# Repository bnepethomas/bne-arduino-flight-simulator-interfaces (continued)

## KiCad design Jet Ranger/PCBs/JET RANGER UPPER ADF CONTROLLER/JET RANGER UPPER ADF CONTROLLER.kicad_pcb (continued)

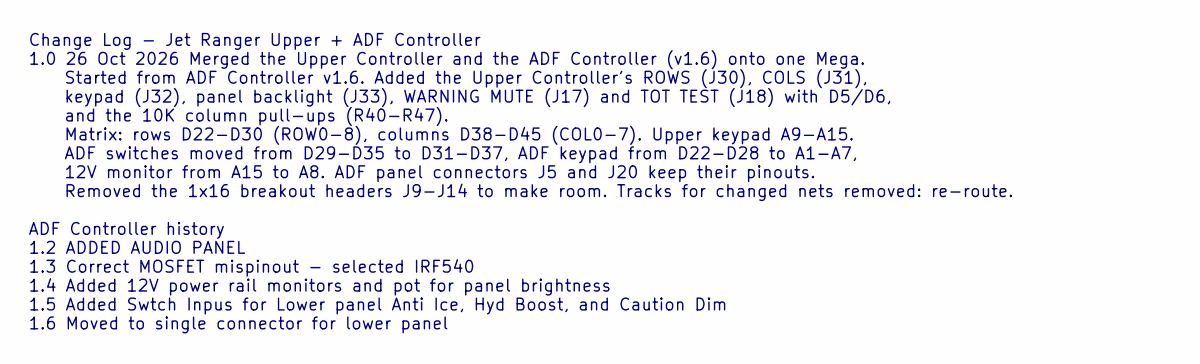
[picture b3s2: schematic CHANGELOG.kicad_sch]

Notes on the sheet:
Change Log - Jet Ranger Upper + ADF Controller 1.0 26 Oct 2026 Merged the Upper Controller and the ADF Controller (v1.6) onto one Mega. Started from ADF Controller v1.6. Added the Upper Controller's ROWS (J30), COLS (J31), keypad (J32), panel backlight (J33), WARNING MUTE (J17) and TOT TEST (J18) w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

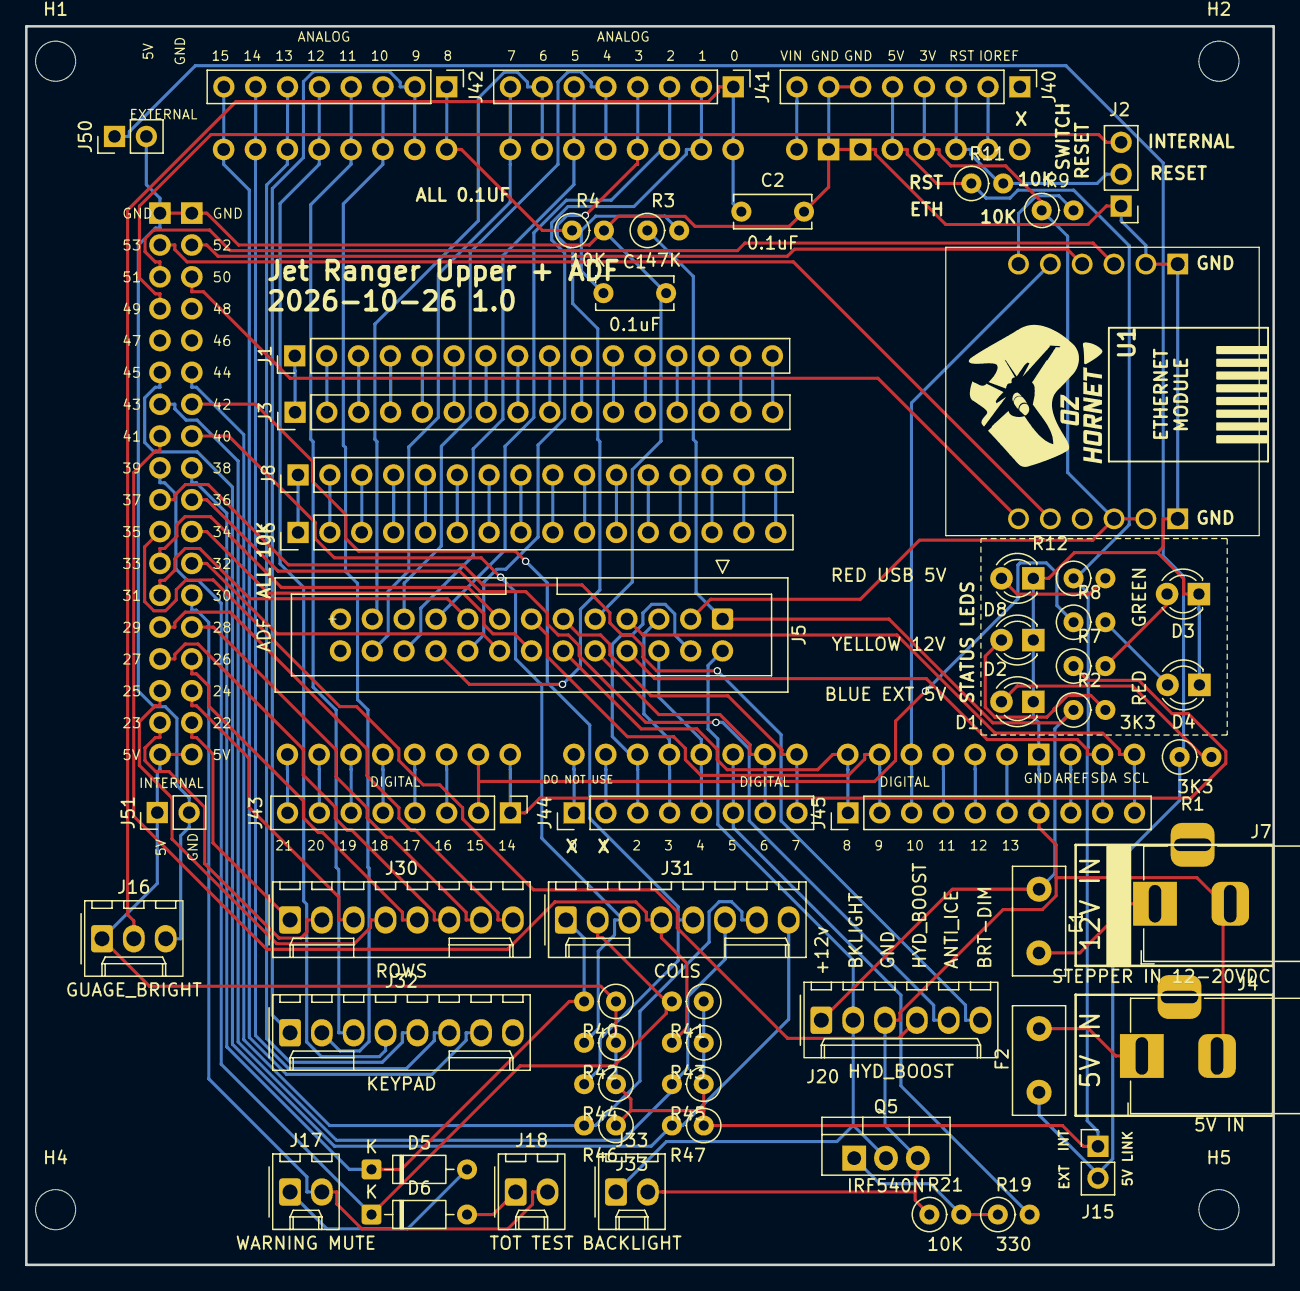
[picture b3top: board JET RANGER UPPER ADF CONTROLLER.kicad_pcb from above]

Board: 2 copper layers, 99.5 x 98.8 mm, 62 parts (0 on the bottom side), 122 nets.

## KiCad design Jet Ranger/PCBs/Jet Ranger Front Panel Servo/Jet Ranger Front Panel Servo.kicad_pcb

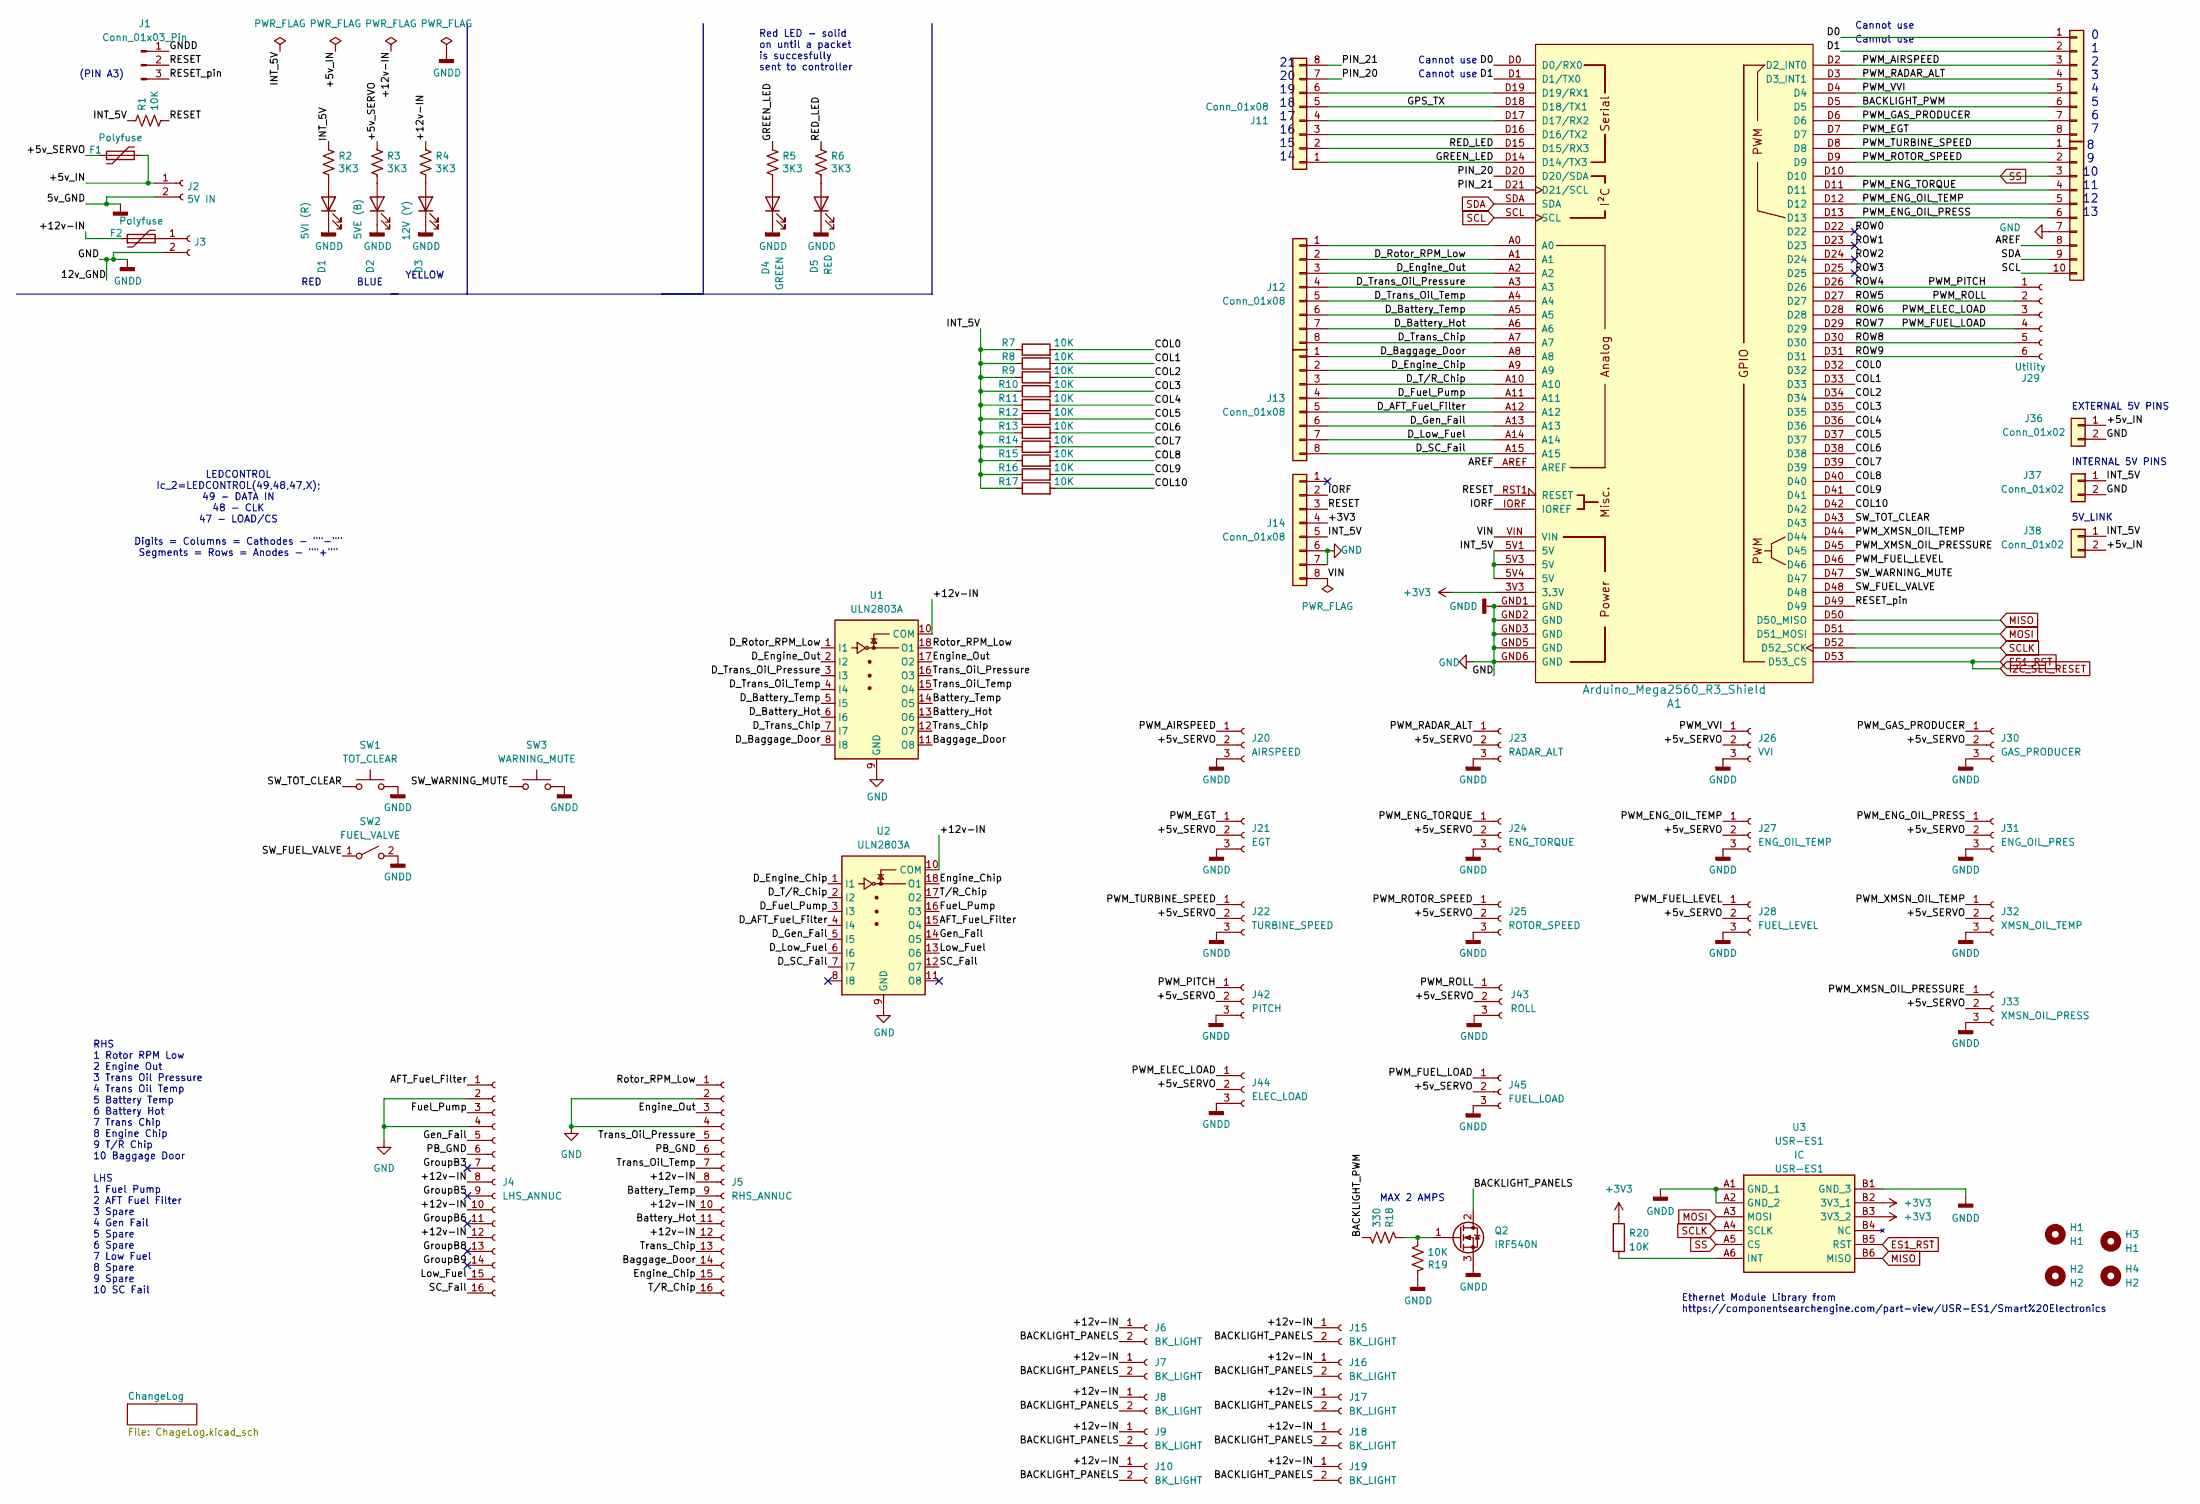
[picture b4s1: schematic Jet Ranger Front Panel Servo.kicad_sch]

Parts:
A1: Arduino_Mega2560_R3_Shield
D1: 5VI (R); LED_D3.0mm
D2: 5VE (B); LED_D3.0mm
D3: 12V (Y); LED_D3.0mm
D4: GREEN; LED_D3.0mm
D5: RED; LED_D3.0mm
F1, F2: Polyfuse; Fuse_Littelfuse_395Series
H1, H3: H1; MountingHole_3.2mm_M3
H2, H4: H2; MountingHole_3.2mm_M3
J1: Conn_01x03_Pin; PinHeader_1x03_P2.54mm_Vertical
J2: 5V IN; BarrelJack_Horizontal
J3: STEPPER IN 12-20VDC; BarrelJack_Horizontal
J4: LHS_ANNUC; IDC-Header_2x08_P2.54mm_Vertical
J5: RHS_ANNUC; IDC-Header_2x08_P2.54mm_Vertical
J6, J7, J8, J9, J10, J15, J16, J17, J18, J19: BK_LIGHT; Molex_KK-254_AE-6410-02A_1x02_P2.54mm_Vertical
J11, J12, J13, J14, J34: Conn_01x08; PinHeader_1x08_P2.54mm_Vertical
J20: AIRSPEED; PinHeader_1x03_P2.54mm_Vertical
J21: EGT; PinHeader_1x03_P2.54mm_Vertical
J22: TURBINE_SPEED; PinHeader_1x03_P2.54mm_Vertical
J23: RADAR_ALT; PinHeader_1x03_P2.54mm_Vertical
J24: ENG_TORQUE; PinHeader_1x03_P2.54mm_Vertical
J25: ROTOR_SPEED; PinHeader_1x03_P2.54mm_Vertical
J26: VVI; PinHeader_1x03_P2.54mm_Vertical
J27: ENG_OIL_TEMP; PinHeader_1x03_P2.54mm_Vertical
J28: FUEL_LEVEL; PinHeader_1x03_P2.54mm_Vertical
J29: Utility; PinHeader_1x06_P2.54mm_Vertical
J30: GAS_PRODUCER; PinHeader_1x03_P2.54mm_Vertical
J31: ENG_OIL_PRES; PinHeader_1x03_P2.54mm_Vertical
J32: XMSN_OIL_TEMP; PinHeader_1x03_P2.54mm_Vertical
J33: XMSN_OIL_PRESS; PinHeader_1x03_P2.54mm_Vertical
J35: Conn_01x10; PinHeader_1x10_P2.54mm_Vertical
J36, J37, J38: Conn_01x02; PinHeader_1x02_P2.54mm_Vertical
J42: PITCH; PinHeader_1x03_P2.54mm_Vertical
J43: ROLL; PinHeader_1x03_P2.54mm_Vertical
J44: ELEC_LOAD; PinHeader_1x03_P2.54mm_Vertical
J45: FUEL_LOAD; PinHeader_1x03_P2.54mm_Vertical
Q2: IRF540N; TO-220-3_Vertical
R1, R7, R8, R9, R10, R11, R12, R13, R14, R15, R16, R17, R19, R20: 10K; R_Axial_DIN0207_L6.3mm_D2.5mm_P2.54mm_Vertical
R2, R3, R4, R5, R6: 3K3; R_Axial_DIN0207_L6.3mm_D2.5mm_P2.54mm_Vertical
R18: 330; R_Axial_DIN0207_L6.3mm_D2.5mm_P2.54mm_Vertical
SW1: TOT_CLEAR; Molex_KK-254_AE-6410-02A_1x02_P2.54mm_Vertical
SW2: FUEL_VALVE; Molex_KK-254_AE-6410-02A_1x02_P2.54mm_Vertical
SW3: WARNING_MUTE; Molex_KK-254_AE-6410-02A_1x02_P2.54mm_Vertical
U1, U2: ULN2803A; DIP-18_W7.62mm
U3: USR-ES1; USRES1; Manufacturer_Part_Number USR-ES1

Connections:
+3V3: A1.3V3 (3.3V), J14.4, R20.1, U3.B2 (3V3_1), U3.B3 (3V3_2)
/+5v_IN: F1.2, J2.1, J36.1, J38.2
/+5v_SERVO: F1.1, J20.2, J21.2, J22.2, J23.2, J24.2, J25.2, J26.2, J27.2, J28.2, J30.2, J31.2, J32.2, J33.2, J42.2, J43.2, J44.2, J45.2, R3.1
/+12v-IN: F2.1, J4.8, J4.10, J4.12, J5.8, J5.10, J5.12, J6.1, J7.1, J8.1, J9.1, J10.1, J15.1, J16.1, J17.1, J18.1, J19.1, R4.1, U1.10 (COM), U2.10 (COM)
/AFT_Fuel_Filter: J4.1, U2.15 (O4)
/AREF: A1.AREF, J35.8
/BACKLIGHT_PANELS: J6.2, J7.2, J8.2, J9.2, J10.2, J15.2, J16.2, J17.2, J18.2, J19.2, Q2.2 (D)
/BACKLIGHT_PWM: A1.D5, J34.6, R18.2
/Baggage_Door: J5.14, U1.11 (O8)
/Battery_Hot: J5.11, U1.13 (O6)
/Battery_Temp: J5.9, U1.14 (O5)
/COL0: A1.D32, R7.2
/COL1: A1.D33, R8.2
/COL2: A1.D34, R9.2
/COL3: A1.D35, R10.2
/COL4: A1.D36, R11.2
/COL5: A1.D37, R12.2
/COL6: A1.D38, R13.2
/COL7: A1.D39, R14.2
/COL8: A1.D40, R15.2
/COL9: A1.D41, R16.2
/COL10: A1.D42, R17.2
/D0: A1.D0 (D0/RX0), J34.1
/D1: A1.D1 (D1/TX0), J34.2
/D_AFT_Fuel_Filter: A1.A12, J13.5, U2.4 (I4)
/D_Baggage_Door: A1.A8, J13.1, U1.8 (I8)
/D_Battery_Hot: A1.A6, J12.7, U1.6 (I6)
/D_Battery_Temp: A1.A5, J12.6, U1.5 (I5)
/D_Engine_Chip: A1.A9, J13.2, U2.1 (I1)
/D_Engine_Out: A1.A2, J12.3, U1.2 (I2)
/D_Fuel_Pump: A1.A11, J13.4, U2.3 (I3)
/D_Gen_Fail: A1.A13, J13.6, U2.5 (I5)
/D_Low_Fuel: A1.A14, J13.7, U2.6 (I6)
/D_Rotor_RPM_Low: A1.A1, J12.2, U1.1 (I1)
/D_SC_Fail: A1.A15, J13.8, U2.7 (I7)
/D_Trans_Chip: A1.A7, J12.8, U1.7 (I7)
/D_Trans_Oil_Pressure: A1.A3, J12.4, U1.3 (I3)
/D_Trans_Oil_Temp: A1.A4, J12.5, U1.4 (I4)
/D_T/R_Chip: A1.A10, J13.3, U2.2 (I2)
/Engine_Chip: J5.15, U2.18 (O1)
/Engine_Out: J5.3, U1.17 (O2)
/Fuel_Pump: J4.3, U2.16 (O3)
/GPS_TX: A1.D18 (D18/TX1), J11.5
/GREEN_LED: A1.D14 (D14/TX3), J11.1, R5.1
/Gen_Fail: J4.5, U2.14 (O5)
/GroupB3: J4.7
/GroupB5: J4.9
/GroupB6: J4.11
/GroupB8: J4.13
/GroupB9: J4.14
/INT_5V: A1.5V1 (5V), A1.5V3 (5V), A1.5V4 (5V), J14.5, J37.1, J38.1, R1.1, R2.1, R7.1, R8.1, R9.1, R10.1, R11.1, R12.1, R13.1, R14.1, R15.1, R16.1, R17.1
/IORF: A1.IORF (IOREF), J14.2
/Low_Fuel: J4.15, U2.13 (O6)
/PB_GND: J4.6, J5.6
/PIN_20: A1.D20 (D20/SDA), J11.7
/PIN_21: A1.D21 (D21/SCL), J11.8
/PWM_AIRSPEED: A1.D2 (D2_INT0), J20.1, J34.3
/PWM_EGT: A1.D7, J21.1, J34.8
/PWM_ELEC_LOAD: A1.D28, J29.3, J44.1
/PWM_ENG_OIL_PRESS: A1.D13, J31.1, J35.6
/PWM_ENG_OIL_TEMP: A1.D12, J27.1, J35.5
/PWM_ENG_TORQUE: A1.D11, J24.1, J35.4
/PWM_FUEL_LEVEL: A1.D46, J28.1
/PWM_FUEL_LOAD: A1.D29, J29.4, J45.1
/PWM_GAS_PRODUCER: A1.D6, J30.1, J34.7
/PWM_PITCH: A1.D26, J29.1, J42.1
/PWM_RADAR_ALT: A1.D3 (D3_INT1), J23.1, J34.4
/PWM_ROLL: A1.D27, J29.2, J43.1
/PWM_ROTOR_SPEED: A1.D9, J25.1, J35.2
/PWM_TURBINE_SPEED: A1.D8, J22.1, J35.1
/PWM_VVI: A1.D4, J26.1, J34.5
/PWM_XMSN_OIL_PRESSURE: A1.D45, J33.1
/PWM_XMSN_OIL_TEMP: A1.D44, J32.1
/RED_LED: A1.D15 (D15/RX3), J11.2, R6.1
/RESET: A1.RST1 (RESET), J1.2, J14.3, R1.2
/RESET_pin: A1.D49, J1.3
/ROW0: A1.D22
/ROW1: A1.D23
/ROW2: A1.D24
/ROW3: A1.D25
/ROW8: A1.D30, J29.5
/ROW9: A1.D31, J29.6
/Rotor_RPM_Low: J5.1, U1.18 (O1)
/SC_Fail: J4.16, U2.12 (O7)
/SW_FUEL_VALVE: A1.D48, SW2.1 (A)
/SW_TOT_CLEAR: A1.D43, SW1.1
/SW_WARNING_MUTE: A1.D47, SW3.1
/Trans_Chip: J5.13, U1.12 (O7)
/Trans_Oil_Pressure: J5.5, U1.16 (O3)
/Trans_Oil_Temp: J5.7, U1.15 (O4)
/T/R_Chip: J5.16, U2.17 (O2)
/VIN: A1.VIN, J14.8
ES1_RST: A1.D53 (D53_CS), U3.B5 (RST)
GND: A1.GND1 (GND), A1.GND2 (GND), A1.GND3 (GND), A1.GND5 (GND), A1.GND6 (GND), D1.1 (K), D2.1 (K), D3.1 (K), D4.1 (K), D5.1 (K), J1.1, J2.2, J3.2, J4.2, J4.4, J5.2, J5.4, J14.6, J14.7, J20.3, J21.3, J22.3, J23.3, J24.3, J25.3, J26.3, J27.3, J28.3, J30.3, J31.3, J32.3, J33.3, J35.7, J36.2, J37.2, J42.3, J43.3, J44.3, J45.3, Q2.3 (S), R19.1, SW1.2, SW2.2 (B), SW3.2, U1.9 (GND), U2.9 (GND), U3.A1 (GND_1), U3.A2 (GND_2), U3.B1 (GND_3)
MISO: A1.D50 (D50_MISO), U3.B6 (MISO)
MOSI: A1.D51 (D51_MOSI), U3.A3 (MOSI)
unnamed: A1.D16 (D16/TX2), J11.3
unnamed: A1.D17 (D17/RX2), J11.4
unnamed: A1.D19 (D19/RX1), J11.6
unnamed: D1.2 (A), R2.2
unnamed: D2.2 (A), R3.2
unnamed: D3.2 (A), R4.2
unnamed: D4.2 (A), R5.2
unnamed: D5.2 (A), R6.2
unnamed: F2.2, J3.1
unnamed: A1.A0, J12.1
unnamed: Q2.1 (G), R18.1, R19.2
unnamed: R20.2, U3.A6 (INT)
SCL: A1.SCL, J35.10
SCLK: A1.D52 (D52_SCK), U3.A4 (SCLK)
SDA: A1.SDA, J35.9
SS: A1.D10, J35.3, U3.A5 (CS)

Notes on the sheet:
YELLOW
MAX 2 AMPS
BLUE
INTERNAL 5V PINS
Ethernet Module Library from https://componentsearchengine.com/part-view/USR-ES1/Smart%20Electronics
Cannot use
RED
(PIN A3)
0 1 2 3 4 5 6 7
LEDCONTROL Ic_2=LEDCONTROL(49,48,47,X); 49 - DATA IN 48 - CLK 47 - LOAD/CS Digits = Columns = Cathodes - ""-"" Segments = Rows = Anodes - ""+""
Red LED - solid on until a packet is succesfully sent to controller
RHS 1 Rotor RPM Low 2 Engine Out 3 Trans Oil Pressure 4 Trans Oil Temp 5 Battery Temp 6 Battery Hot 7 Trans Chip 8 Engine Chip 9 T/R Chip 10 Baggage Door LHS 1 Fuel Pump 2 AFT Fuel Filter 3 Spare 4 Gen Fail 5 Spare 6 Spare 7 Low Fuel 8 Spare 9 Spare 10 SC Fail
5V_LINK
21 20 19 18 17 16 15 14
EXTERNAL 5V PINS
8 9 10 11 12 13

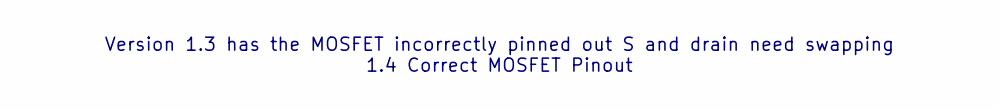
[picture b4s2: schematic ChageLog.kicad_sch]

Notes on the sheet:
Version 1.3 has the MOSFET incorrectly pinned out S and drain need swapping 1.4 Correct MOSFET Pinout

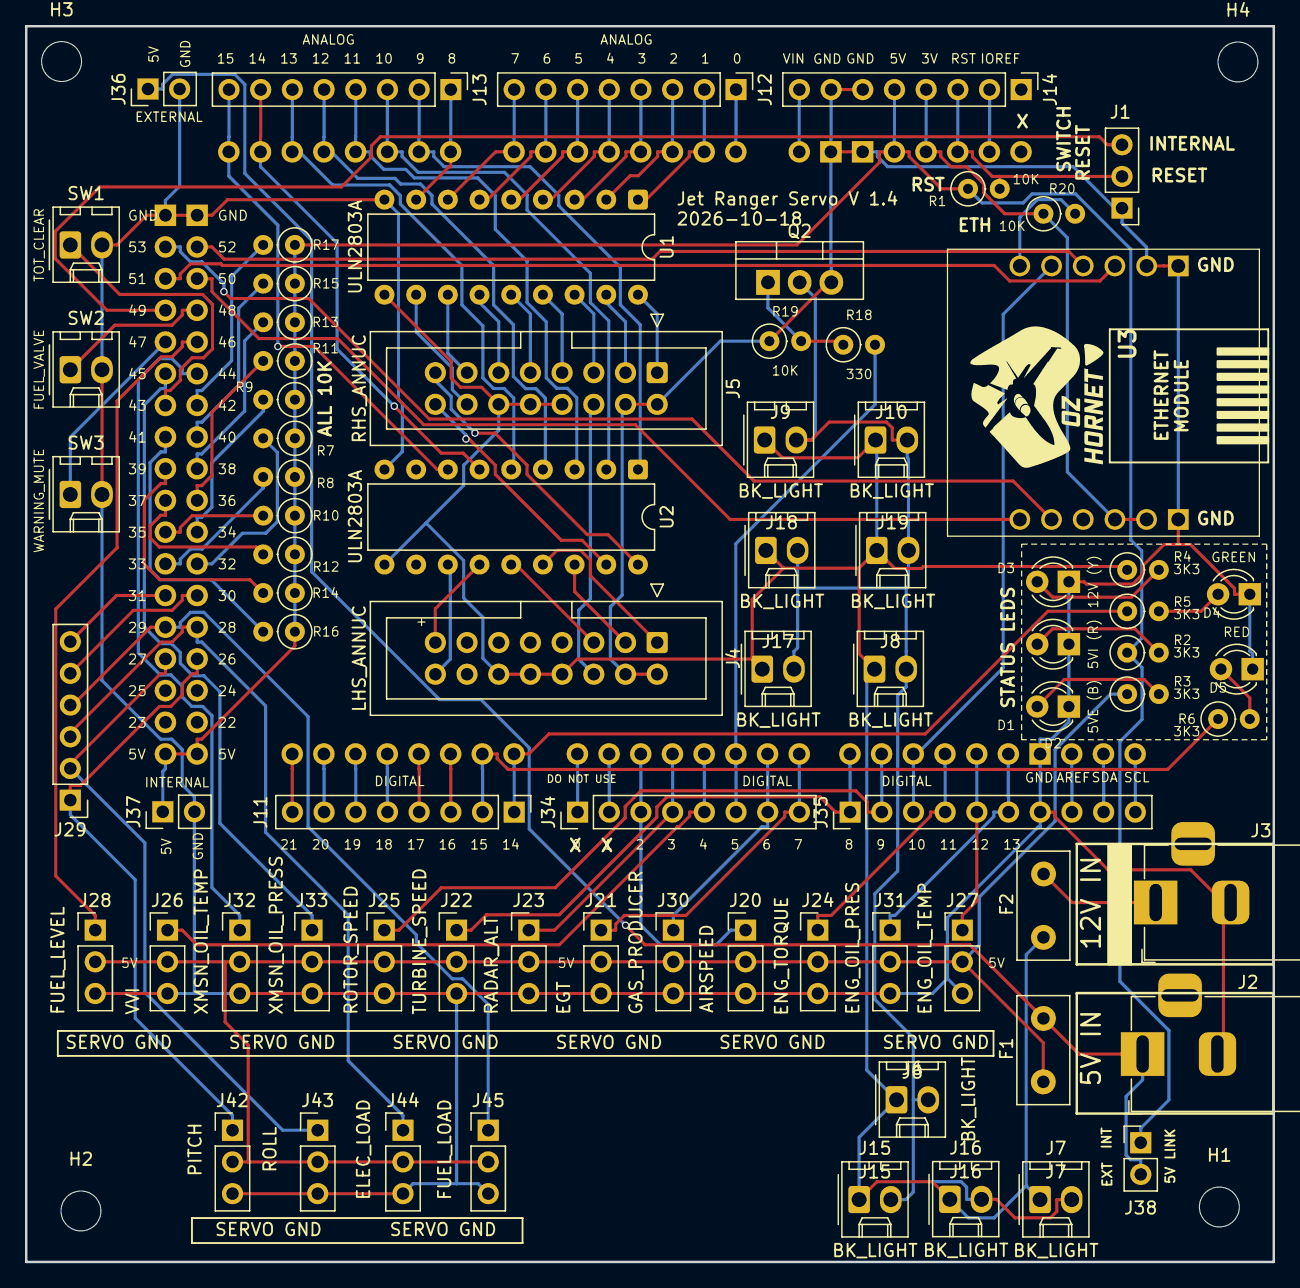
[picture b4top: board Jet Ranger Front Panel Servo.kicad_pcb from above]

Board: 2 copper layers, 100.0 x 99.1 mm, 81 parts (0 on the bottom side), 103 nets.

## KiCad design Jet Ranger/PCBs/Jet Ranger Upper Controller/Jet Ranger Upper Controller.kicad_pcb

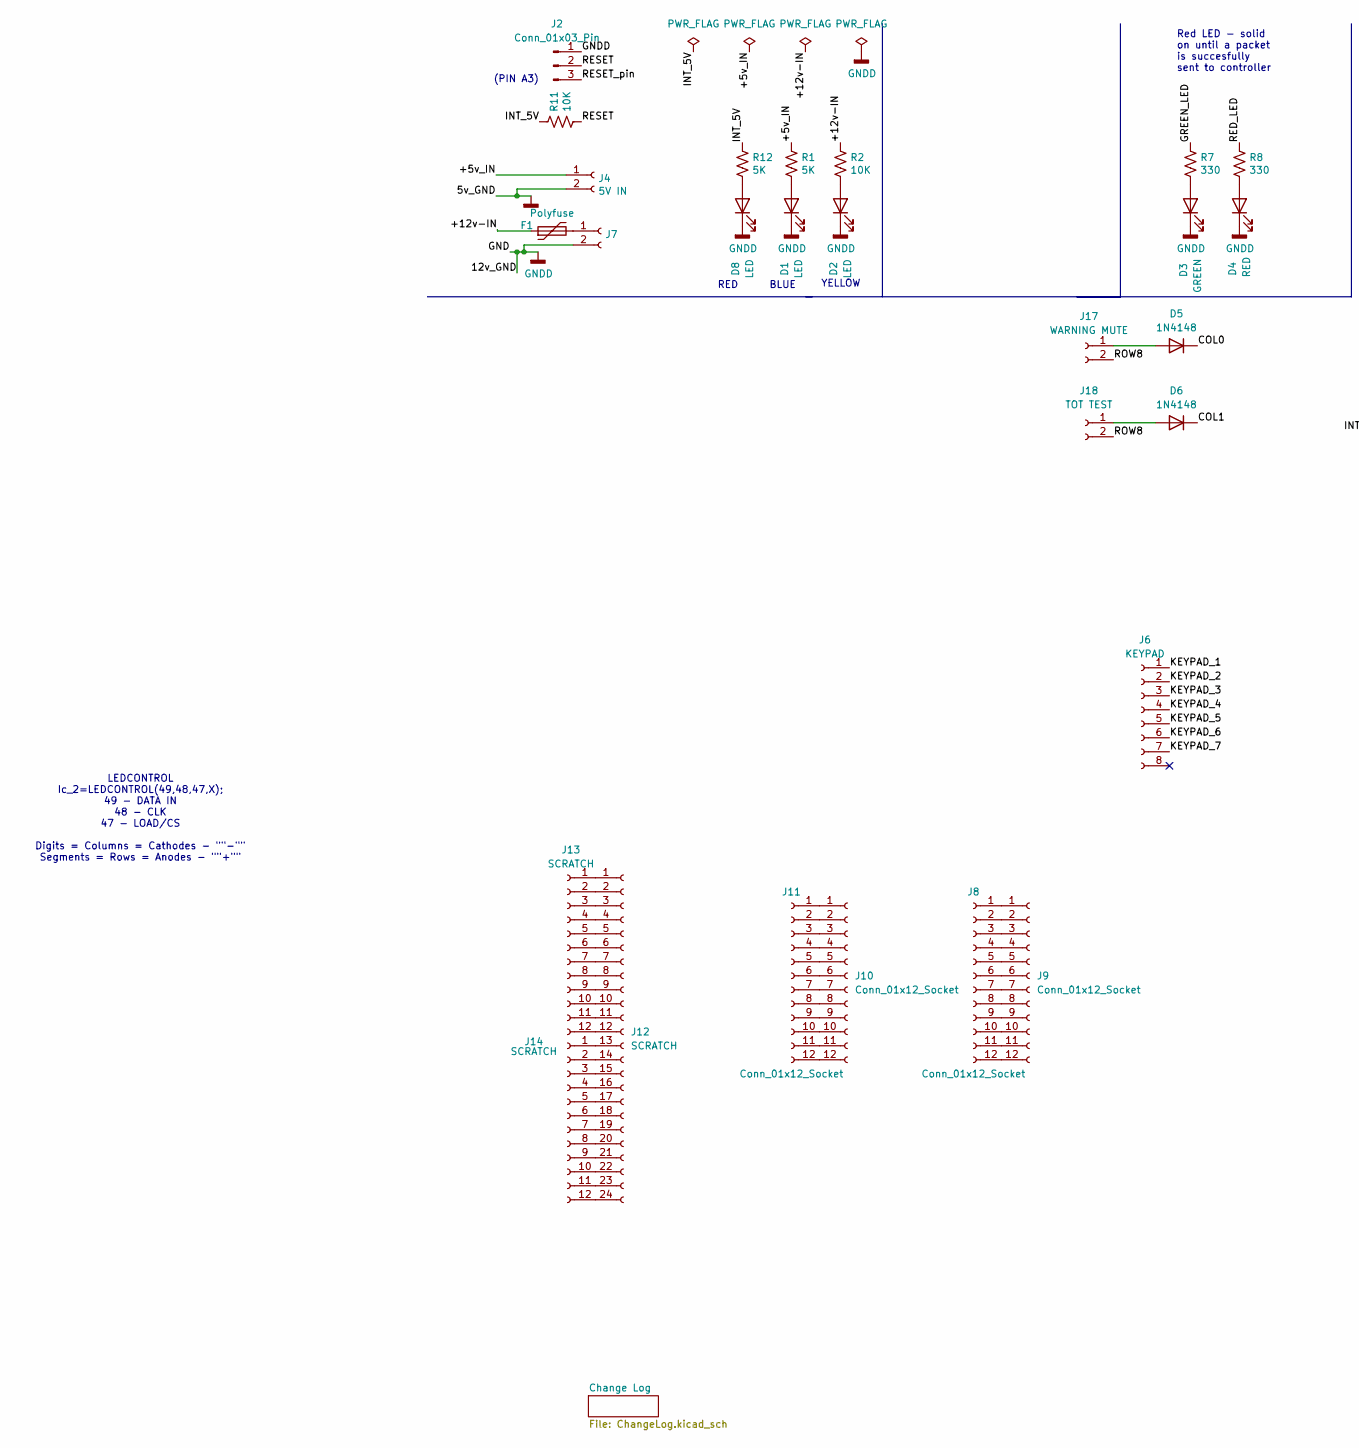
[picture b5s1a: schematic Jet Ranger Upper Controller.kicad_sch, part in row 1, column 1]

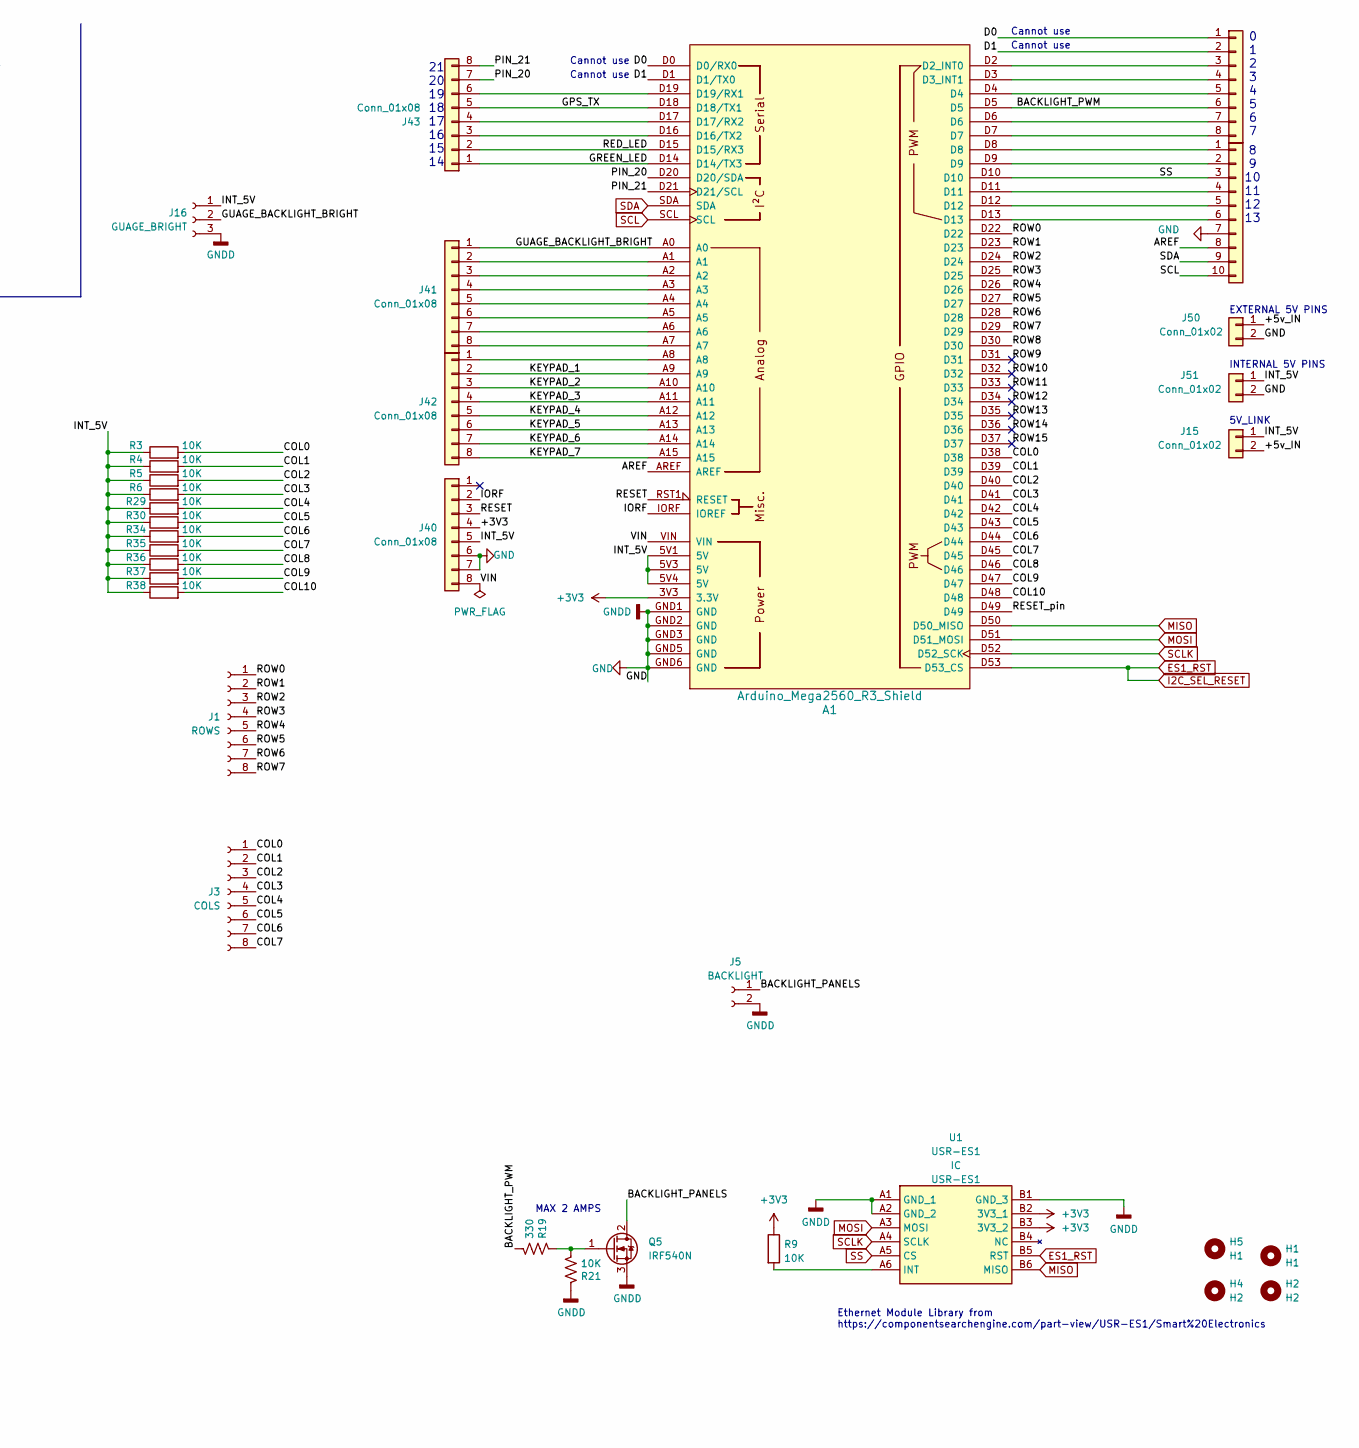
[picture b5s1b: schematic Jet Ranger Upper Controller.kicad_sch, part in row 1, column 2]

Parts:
A1: Arduino_Mega2560_R3_Shield
D1, D2, D8: LED; LED_D3.0mm
D3: GREEN; LED_D3.0mm
D4: RED; LED_D3.0mm
D5, D6: 1N4148; D_DO-35_SOD27_P7.62mm_Horizontal
F1: Polyfuse; Fuse_Bourns_MF-RG400
H1, H5: H1; MountingHole_3.2mm_M3
H2, H4: H2; MountingHole_3.2mm_M3
J1: ROWS; Molex_KK-254_AE-6410-08A_1x08_P2.54mm_Vertical
J2: Conn_01x03_Pin; PinHeader_1x03_P2.54mm_Vertical
J3: COLS; Molex_KK-254_AE-6410-08A_1x08_P2.54mm_Vertical
J4: 5V IN; BarrelJack_Horizontal
J5: BACKLIGHT; Molex_KK-254_AE-6410-02A_1x02_P2.54mm_Vertical
J6: KEYPAD; Molex_KK-254_AE-6410-08A_1x08_P2.54mm_Vertical
J7: STEPPER IN 12-20VDC; BarrelJack_Horizontal
J8, J9, J10, J11: Conn_01x12_Socket; PinHeader_1x12_P2.54mm_Vertical
J12: SCRATCH; IDC-Header_2x12_P2.54mm_Vertical
J13, J14: SCRATCH; PinHeader_1x12_P2.54mm_Vertical
J15, J50, J51: Conn_01x02; PinHeader_1x02_P2.54mm_Vertical
J16: GUAGE_BRIGHT; Molex_KK-254_AE-6410-03A_1x03_P2.54mm_Vertical
J17: WARNING MUTE; Molex_KK-254_AE-6410-02A_1x02_P2.54mm_Vertical
J18: TOT TEST; Molex_KK-254_AE-6410-02A_1x02_P2.54mm_Vertical
J40, J41, J42, J43, J44: Conn_01x08; PinHeader_1x08_P2.54mm_Vertical
J45: Conn_01x10; PinHeader_1x10_P2.54mm_Vertical
Q5: IRF540N; TO-220-3_Vertical
R1, R12: 5K; R_Axial_DIN0207_L6.3mm_D2.5mm_P2.54mm_Vertical
R2, R3, R4, R5, R6, R9, R11, R21, R29, R30, R34, R35, R36, R37, R38: 10K; R_Axial_DIN0207_L6.3mm_D2.5mm_P2.54mm_Vertical
R7, R8, R19: 330; R_Axial_DIN0207_L6.3mm_D2.5mm_P2.54mm_Vertical
U1: USR-ES1; USRES1; Manufacturer_Part_Number USR-ES1

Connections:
+3V3: A1.3V3 (3.3V), J40.4, R9.1, U1.B2 (3V3_1), U1.B3 (3V3_2)
/+5v_IN: J4.1, J15.2, J50.1, R1.1
/+12v-IN: F1.1, R2.1
/AREF: A1.AREF, J45.8
/BACKLIGHT_PANELS: J5.1, Q5.2 (D)
/BACKLIGHT_PWM: A1.D5, J44.6, R19.2
/COL0: A1.D38, D5.1 (K), J3.1, R3.2
/COL1: A1.D39, D6.1 (K), J3.2, R4.2
/COL2: A1.D40, J3.3, R5.2
/COL3: A1.D41, J3.4, R6.2
/COL4: A1.D42, J3.5, R29.2
/COL5: A1.D43, J3.6, R30.2
/COL6: A1.D44, J3.7, R34.2
/COL7: A1.D45, J3.8, R35.2
/COL8: A1.D46, R36.2
/COL9: A1.D47, R37.2
/COL10: A1.D48, R38.2
/D0: A1.D0 (D0/RX0), J44.1
/D1: A1.D1 (D1/TX0), J44.2
/GPS_TX: A1.D18 (D18/TX1), J43.5
/GREEN_LED: A1.D14 (D14/TX3), J43.1, R7.1
/GUAGE_BACKLIGHT_BRIGHT: A1.A0, J16.2, J41.1
/INT_5V: A1.5V1 (5V), A1.5V3 (5V), A1.5V4 (5V), J15.1, J16.1, J40.5, J51.1, R3.1, R4.1, R5.1, R6.1, R11.1, R12.1, R29.1, R30.1, R34.1, R35.1, R36.1, R37.1, R38.1
/IORF: A1.IORF (IOREF), J40.2
/KEYPAD_1: A1.A9, J6.1, J42.2
/KEYPAD_2: A1.A10, J6.2, J42.3
/KEYPAD_3: A1.A11, J6.3, J42.4
/KEYPAD_4: A1.A12, J6.4, J42.5
/KEYPAD_5: A1.A13, J6.5, J42.6
/KEYPAD_6: A1.A14, J6.6, J42.7
/KEYPAD_7: A1.A15, J6.7, J42.8
/PIN_20: A1.D20 (D20/SDA), J43.7
/PIN_21: A1.D21 (D21/SCL), J43.8
/RED_LED: A1.D15 (D15/RX3), J43.2, R8.1
/RESET: A1.RST1 (RESET), J2.2, J40.3, R11.2
/RESET_pin: A1.D49, J2.3
/ROW0: A1.D22, J1.1
/ROW1: A1.D23, J1.2
/ROW2: A1.D24, J1.3
/ROW3: A1.D25, J1.4
/ROW4: A1.D26, J1.5
/ROW5: A1.D27, J1.6
/ROW6: A1.D28, J1.7
/ROW7: A1.D29, J1.8
/ROW8: A1.D30, J17.2, J18.2
/ROW9: A1.D31
/ROW10: A1.D32
/ROW11: A1.D33
/ROW12: A1.D34
/ROW13: A1.D35
/ROW14: A1.D36
/ROW15: A1.D37
/VIN: A1.VIN, J40.8
ES1_RST: A1.D53 (D53_CS), U1.B5 (RST)
GND: A1.GND1 (GND), A1.GND2 (GND), A1.GND3 (GND), A1.GND5 (GND), A1.GND6 (GND), D1.1 (K), D2.1 (K), D3.1 (K), D4.1 (K), D8.1 (K), J2.1, J4.2, J5.2, J7.2, J16.3, J40.6, J40.7, J45.7, J50.2, J51.2, Q5.3 (S), R21.1, U1.A1 (GND_1), U1.A2 (GND_2), U1.B1 (GND_3)
MISO: A1.D50 (D50_MISO), U1.B6 (MISO)
MOSI: A1.D51 (D51_MOSI), U1.A3 (MOSI)
unnamed: A1.D2 (D2_INT0), J44.3
unnamed: A1.D3 (D3_INT1), J44.4
unnamed: A1.D16 (D16/TX2), J43.3
unnamed: A1.D17 (D17/RX2), J43.4
unnamed: A1.D19 (D19/RX1), J43.6
unnamed: D1.2 (A), R1.2
unnamed: D2.2 (A), R2.2
unnamed: D3.2 (A), R7.2
unnamed: D4.2 (A), R8.2
unnamed: D5.2 (A), J17.1
unnamed: D6.2 (A), J18.1
unnamed: D8.2 (A), R12.2
unnamed: F1.2, J7.1
unnamed: J8.1, J9.1
unnamed: J8.2, J9.2
unnamed: J8.3, J9.3
unnamed: J8.4, J9.4
unnamed: J8.5, J9.5
unnamed: J8.6, J9.6
unnamed: J8.7, J9.7
unnamed: J8.8, J9.8
unnamed: J8.9, J9.9
unnamed: J8.10, J9.10
unnamed: J8.11, J9.11
unnamed: J8.12, J9.12
unnamed: J10.1, J11.1
unnamed: J10.2, J11.2
unnamed: J10.3, J11.3
unnamed: J10.4, J11.4
unnamed: J10.5, J11.5
unnamed: J10.6, J11.6
unnamed: J10.7, J11.7
unnamed: J10.8, J11.8
unnamed: J10.9, J11.9
unnamed: J10.10, J11.10
unnamed: J10.11, J11.11
unnamed: J10.12, J11.12
unnamed: J12.1, J13.1
unnamed: J12.2, J13.2
unnamed: J12.3, J13.3
unnamed: J12.4, J13.4
unnamed: J12.5, J13.5
unnamed: J12.6, J13.6
unnamed: J12.7, J13.7
unnamed: J12.8, J13.8
unnamed: J12.9, J13.9
unnamed: J12.10, J13.10
unnamed: J12.11, J13.11
unnamed: J12.12, J13.12
unnamed: J12.13, J14.1
unnamed: J12.14, J14.2
unnamed: J12.15, J14.3
unnamed: J12.16, J14.4
unnamed: J12.17, J14.5
unnamed: J12.18, J14.6
unnamed: J12.19, J14.7
unnamed: J12.20, J14.8
unnamed: J12.21, J14.9
unnamed: J12.22, J14.10
unnamed: J12.23, J14.11
unnamed: J12.24, J14.12
unnamed: A1.A1, J41.2
unnamed: A1.A2, J41.3
unnamed: A1.A3, J41.4
unnamed: A1.A4, J41.5
unnamed: A1.A5, J41.6
unnamed: A1.A6, J41.7
unnamed: A1.A7, J41.8
unnamed: A1.A8, J42.1
unnamed: A1.D4, J44.5
unnamed: A1.D6, J44.7
unnamed: A1.D7, J44.8
unnamed: A1.D8, J45.1
unnamed: A1.D9, J45.2
unnamed: A1.D11, J45.4
unnamed: A1.D12, J45.5
unnamed: A1.D13, J45.6
unnamed: Q5.1 (G), R19.1, R21.2
unnamed: R9.2, U1.A6 (INT)
SCL: A1.SCL, J45.10
SCLK: A1.D52 (D52_SCK), U1.A4 (SCLK)
SDA: A1.SDA, J45.9
SS: A1.D10, J45.3, U1.A5 (CS)

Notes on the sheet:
YELLOW
MAX 2 AMPS
BLUE
INTERNAL 5V PINS
Ethernet Module Library from https://componentsearchengine.com/part-view/USR-ES1/Smart%20Electronics
Cannot use
RED
(PIN A3)
0 1 2 3 4 5 6 7
LEDCONTROL Ic_2=LEDCONTROL(49,48,47,X); 49 - DATA IN 48 - CLK 47 - LOAD/CS Digits = Columns = Cathodes - ""-"" Segments = Rows = Anodes - ""+""
Red LED - solid on until a packet is succesfully sent to controller
5V_LINK
21 20 19 18 17 16 15 14
EXTERNAL 5V PINS
8 9 10 11 12 13

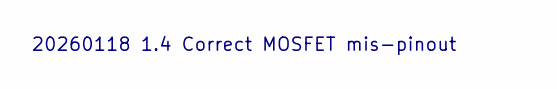
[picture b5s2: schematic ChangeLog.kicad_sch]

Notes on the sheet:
20260118 1.4 Correct MOSFET mis-pinout

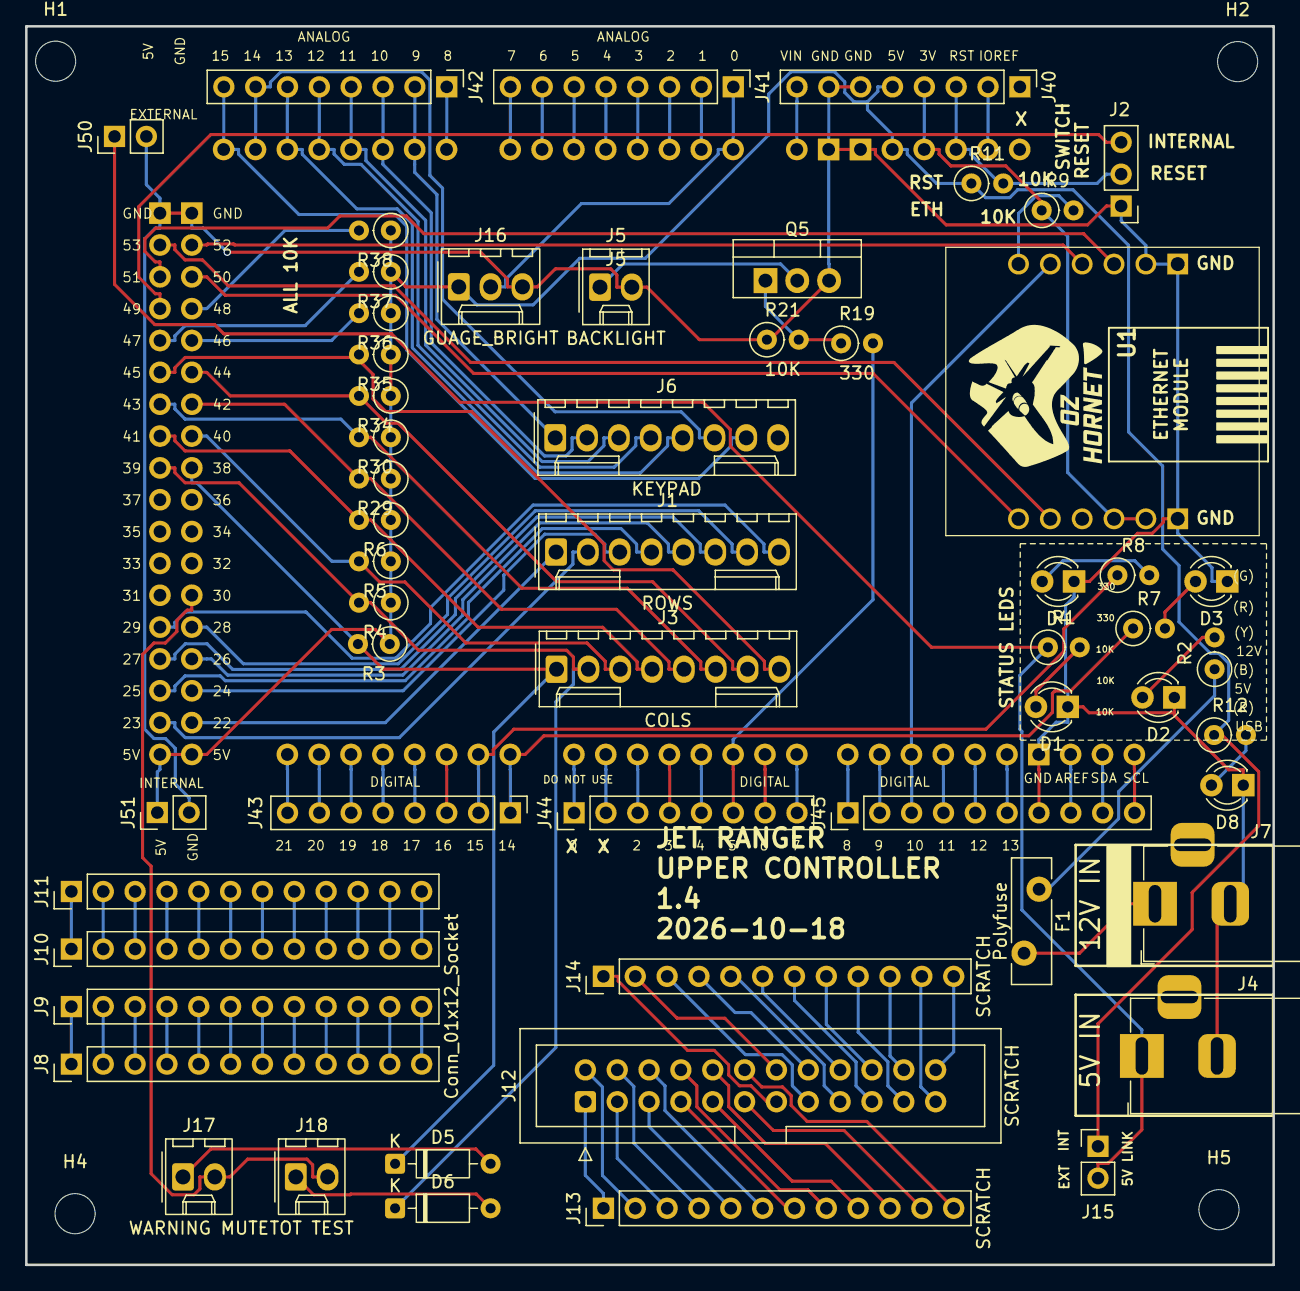
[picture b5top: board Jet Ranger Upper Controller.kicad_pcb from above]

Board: 2 copper layers, 99.5 x 98.8 mm, 61 parts (0 on the bottom side), 133 nets.
